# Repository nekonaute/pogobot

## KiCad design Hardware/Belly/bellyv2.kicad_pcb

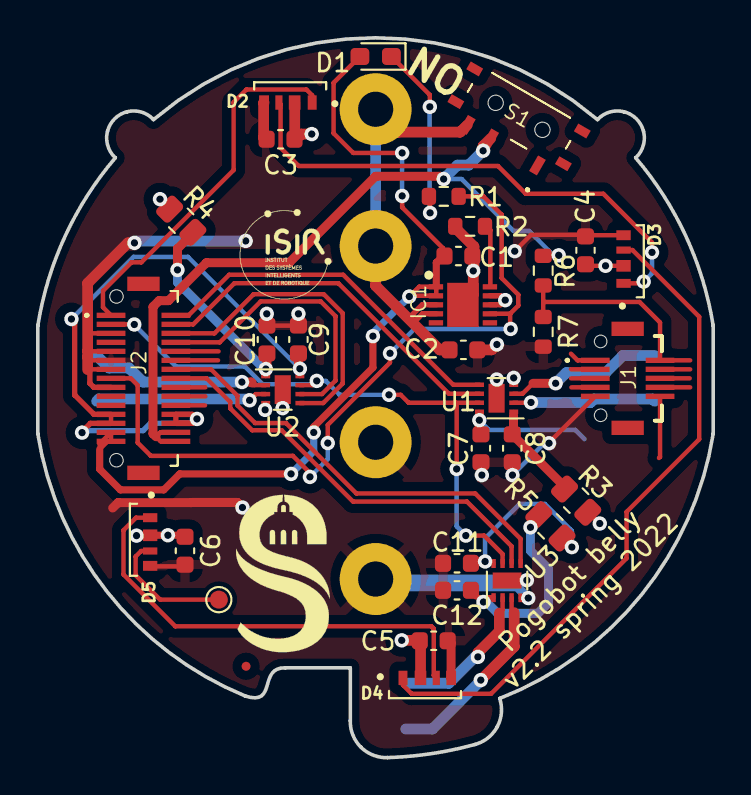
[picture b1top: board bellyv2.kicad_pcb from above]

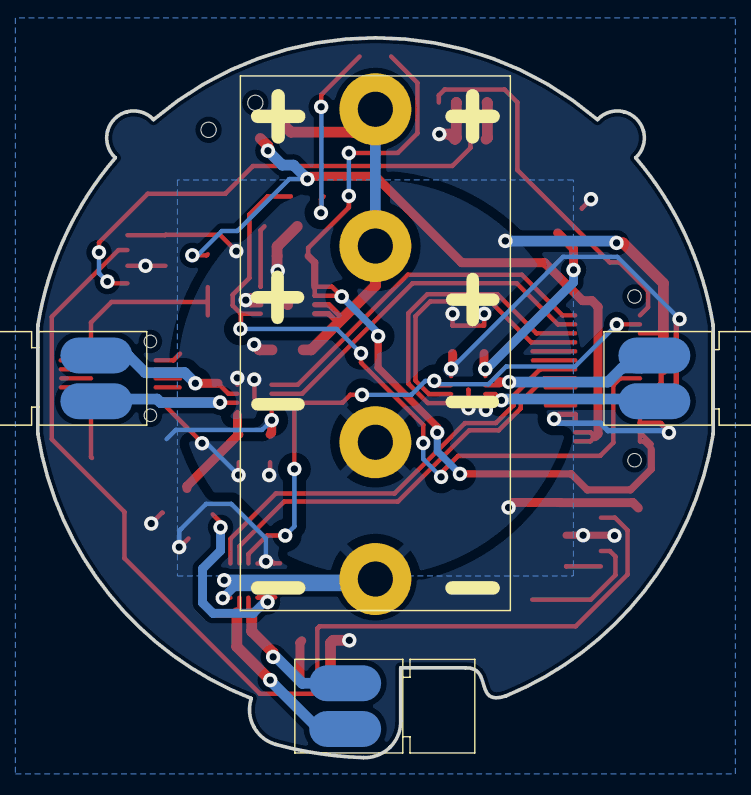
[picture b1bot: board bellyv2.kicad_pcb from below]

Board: 2 copper layers, 37.5 x 40.0 mm, 36 parts (4 on the bottom side), 30 nets.

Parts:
C1, C2: 4.7uF; C_0603_1608Metric
C3, C4, C5, C6: 1uF; C_0603_1608Metric
C7, C8, C9, C10, C11, C12: 100n; C_0603_1608Metric
D1: LED; LED_0603_1608Metric_Pad1.05x0.95mm_HandSolder
D2, D3, D4, D5: IN-PI42TASPRPGPB; LED_IN-PI42TASPRPGPB
IC1: MCP73123-22SI_MF; SON50P300X300X100-11N-D
J1: 10132797-015100LF; 10132797015100LF
J2: 10132797-035100LF; 10132797035100LF
J3: A/AA PCB Battery clip; CR2_Holder
M1, M2, M3: Motor_DC; Vibrating_5x6mm_DC_motor
R1: 1K; R_0603_1608Metric
R2, R6, R7: 10K; R_0603_1608Metric
R3, R4, R5: 0; R_0805_2012Metric
S1: MSK12C02
TP4: RGB_Out; TestPoint_Pad_D1.0mm
U1, U2, U3: DRV8837C; WSON-8-1EP_2x2mm_P0.5mm_EP0.9x1.6mm

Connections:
+3V3: C3.1, C4.1, C5.1, C6.1, C7.1, C9.1, C11.1, D2.2 (VDD), D3.2 (VDD), D4.2 (VDD), D5.2 (VDD), J2.12, J2.13, J2.18, J2.19, R3.1, R4.1, R5.1, U1.8 (VCC), U2.8 (VCC), U3.8 (VCC)
+5V: C1.1, D1.2 (A), IC1.1 (VDD_1), IC1.2 (VDD_2), J2.14, J2.15
+BATT: J2.16, J2.17, R6.1, S1.B1 (COM)
/CH7: J1.10, R6.2, R7.1
/prog: IC1.10 (PROG), R2.2
GND: C1.2, C2.2, C3.2, C4.2, C5.2, C6.2, C7.2, C8.2, C9.2, C10.2, C11.2, C12.2, D2.4 (GND), D3.4 (GND), D4.4 (GND), D5.4 (GND), IC1.8 (VSS_1), IC1.9 (VSS_2), IC1.11 (EP), J1.5, J2.3, J2.5, J2.6, J2.7, J2.9, J3.2, R2.1, R7.2, U1.4 (GND), U1.9 (GND), U2.4 (GND), U2.9 (GND), U3.4 (GND), U3.9 (GND)
GPIO0: J2.30, U1.5 (IN2)
GPIO1: J2.29, U1.6 (IN1)
GPIO2: J2.28, U2.5 (IN2)
GPIO3: J2.27, U2.6 (IN1)
GPIO6: J2.24, U3.5 (IN2)
GPIO7: J2.23, U3.6 (IN1)
GPIO8: J2.2, U1.7 (~SLEEP), U2.7 (~SLEEP), U3.7 (~SLEEP)
LED_CHARGE: IC1.7 (STAT), J2.8, R1.2
unnamed: C2.1, IC1.3 (VBAT_1), IC1.4 (VBAT_2), J3.1, S1.C1 (NO)
unnamed: C8.1, R3.2, U1.1 (VM)
unnamed: C10.1, R4.2, U2.1 (VM)
unnamed: C12.1, R5.2, U3.1 (VM)
unnamed: D1.1 (K), R1.1
unnamed: D2.3 (DOUT), D3.1 (DIN)
unnamed: D3.3 (DOUT), D4.1 (DIN)
unnamed: D4.3 (DOUT), D5.1 (DIN)
unnamed: D5.3 (DOUT), TP4.1
unnamed: M1.1 (+), U1.2 (OUT1)
unnamed: M1.2 (-), U1.3 (OUT2)
unnamed: M2.1 (+), U2.2 (OUT1)
unnamed: M2.2 (-), U2.3 (OUT2)
unnamed: M3.1 (+), U3.2 (OUT1)
unnamed: M3.2 (-), U3.3 (OUT2)
RGB_LED_OUT: D2.1 (DIN), J2.1

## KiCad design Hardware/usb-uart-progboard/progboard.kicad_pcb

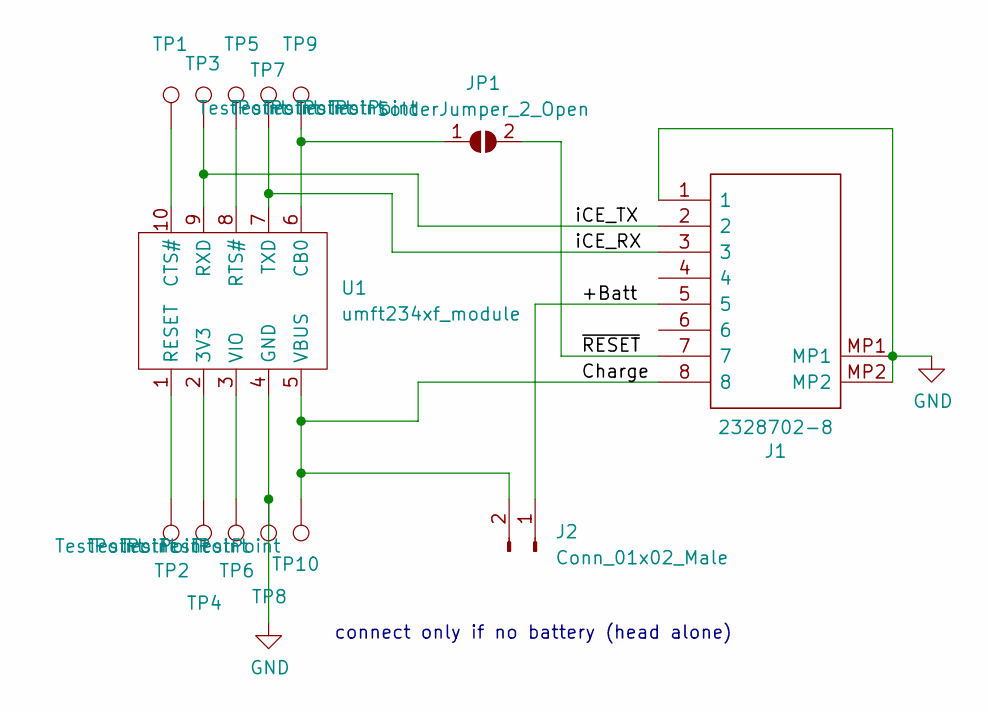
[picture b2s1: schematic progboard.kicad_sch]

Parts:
J1: 2328702-8; 23287028; Manufacturer_Part_Number 2328702-8; Mouser Part Number 571-2328702-8
J2: Conn_01x02_Male; PinHeader_1x02_P2.54mm_Horizontal
JP1: SolderJumper_2_Open; SolderJumper-2_P1.3mm_Open_RoundedPad1.0x1.5mm
TP1, TP2, TP3, TP4, TP5, TP6, TP7, TP8, TP9, TP10: TestPoint; TestPoint_Pad_D1.5mm
U1: umft234xf_module; umft234xf

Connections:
/+Batt: J1.5, J2.1
/Charge: J1.8, J2.2, TP10.1, U1.5 (VBUS)
/iCE_RX: J1.3, TP7.1, U1.7 (TXD)
/iCE_TX: J1.2, TP3.1, U1.9 (RXD)
/~RESET: J1.7, JP1.2 (B)
GND: J1.1, J1.MP1, J1.MP2, TP8.1, U1.4 (GND)
unnamed: JP1.1 (A), TP9.1, U1.6 (CB0)
unnamed: TP1.1, U1.10 (CTS#)
unnamed: TP2.1, U1.1 (RESET)
unnamed: TP4.1, U1.2 (3V3)
unnamed: TP5.1, U1.8 (RTS#)
unnamed: TP6.1, U1.3 (VIO)

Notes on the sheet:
connect only if no battery (head alone)

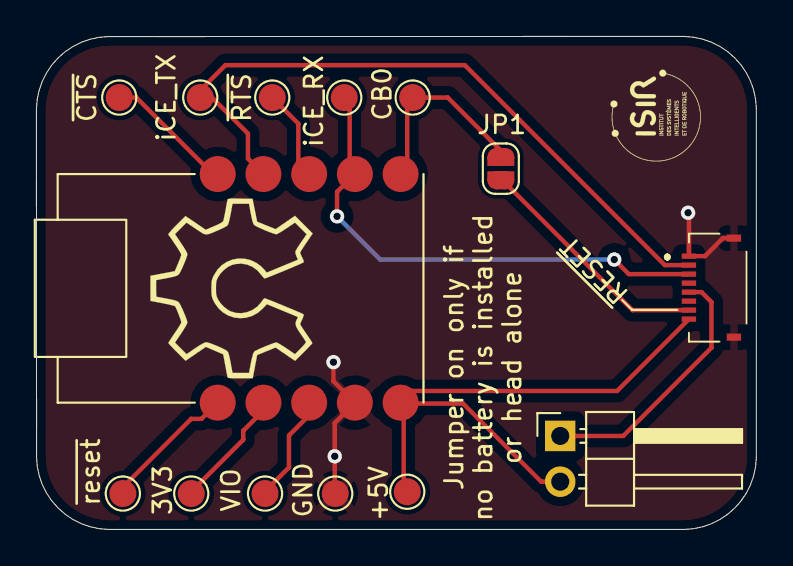
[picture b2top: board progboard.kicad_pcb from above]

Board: 2 copper layers, 40.0 x 27.4 mm, 14 parts (0 on the bottom side), 12 nets.
